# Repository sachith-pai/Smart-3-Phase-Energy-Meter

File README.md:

# Smart-3-Phase-Enrgy-Meter
An ESPHome-based energy meter powered by PZEM-004T V4 and Seed Studio Xiao ESP32-C6/ESP32-C3
 <div align="center">
  
</div>

## Componenets
1. [Seed Studio Xiao C6](https://www.seeedstudio.com/Seeed-Studio-XIAO-ESP32C6-p-5884.html) OR Xiao C3
2. [PZEM-004T V4](https://robu.in/product/pzem-004t-with-coil-ct-with-outcasehot-ac-meter/)
3. [SSD1306 0.96 OLED Display](https://quartzcomponents.com/products/oled-display-0-96-inch-i2c-interface-4-pin-blue-ssd1306)
4. [Hi-Link 5V 5W PSU (HLK 5M05)](https://robu.in/product/hlk-5m05-5v-5w-switch-power-supply-module/?gad_source=1&gad_campaignid=17427802559&gbraid=0AAAAADvLFWdyY2DiddMgGUwxKQrgYGrId&gclid=CjwKCAjwq6DQBhBVEiwA4ZD5XINyfahhBX2IyH8qCKN4hPUuXApgPumztB-3vMhQIovpEZZ0PR9EfBoCjpYQAvD_BwE)
5. [1N5819 Schottky barrier diode](https://robu.in/product/1n5819-1w-diode-pack-of-30/)
6. [4 Pin JST XH Male Connector - 2.54mm pitch](https://quartzcomponents.com/products/4-pin-jst-xh-male-connector-5-24mm-pitch)
7. [4 Pin JST Female to Female Connector - 2.54mm Pitch](https://quartzcomponents.com/products/4-pin-jst-female-to-female-connector-2-54mm-pitch)
8. [2 Pin Screw Terminal Block - 5mm Pitch](https://quartzcomponents.com/products/2-pin-pcb-mount-terminal-block-screw-type)
9. [Transparent Junction Box(180X130X100)](https://amzn.in/d/0d2WMVyG)

## Schematics 
 <div align="center">
  
</div>

> [!NOTE]
>If ESPHome is unable to read from all three PZEM modules simultaneously, it is because multiple devices prevent the signal from dropping close enough to GND. To fix this, it is recommended to place a 1N5819  Schottky diode on the TX line of each PZEM .  Which I have included in the schematics as well as  in the PCB 

## PCB 

<table align="center">
  <tr>
    <td align="center">
      <br>
    </td>
    <td align="center">
      <br>
    </td>

  </tr>
</table>

## Installtion 
1. Download the configuration of your board (c3 or c6), which can be found [HERE](/ESPHOME), and simply go to your ESPHome instance and "import from file" as shown in the picture 
  <div align="center">
  
</div>
2. Set the address to each of the Pzem-004T's using a USB to TTL Serial Adapter as follows

> [!NOTE]
> The address can also be changed in ESPHome, but this is recommended 

|Phase|Address|
|:--:|:--:|
|P1|0x01|
|P2|0x02|
|P3|0x03|

## Reference
1. [ESPHome Pzem-004T Docs](https://esphome.io/components/sensor/pzemac/)
2. [ESPHome SSD1306 OLED Display Docs](https://esphome.io/components/display/ssd1306/)
3. [Multiple Pzem Communication Error forum](https://community.home-assistant.io/t/pzem-004t-v4-0-esphome-not-able-to-read-simultaneously-from-all-3-pzems/957478/2)

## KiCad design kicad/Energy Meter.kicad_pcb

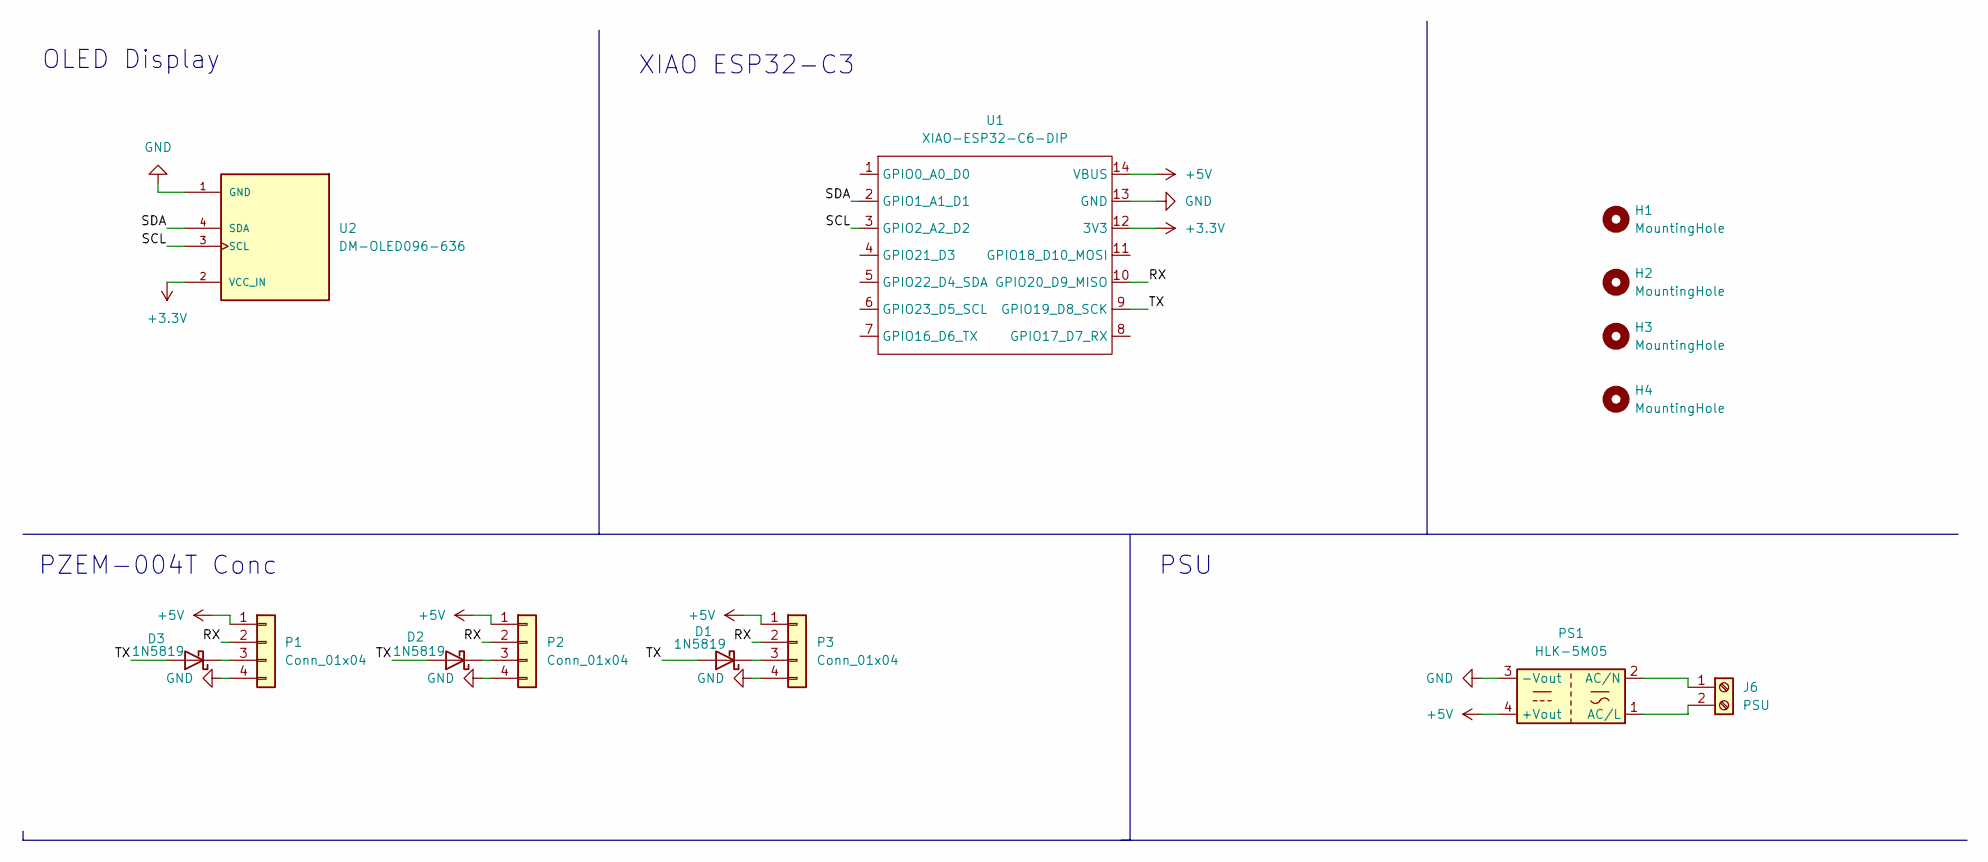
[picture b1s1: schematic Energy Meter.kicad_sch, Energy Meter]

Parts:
D1, D2, D3: 1N5819; D_DO-41_SOD81_P10.16mm_Horizontal
H1, H2, H3, H4: MountingHole; MountingHole_3.2mm_M3_ISO7380_Pad
J6: PSU; TerminalBlock_MaiXu_MX126-5.0-02P_1x02_P5.00mm
P1, P2, P3: Conn_01x04; PinHeader_1x04_P2.54mm_Vertical
PS1: HLK-5M05; Converter_ACDC_Hi-Link_HLK-5Mxx
U1: XIAO-ESP32-C6-DIP
U2: DM-OLED096-636; MODULE_DM-OLED096-636; PARTREV 2018-09-10

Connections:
+3.3V: U1.12 (3V3), U2.2 (VCC_IN)
+5V: P1.1, P2.1, P3.1, PS1.4 (+Vout), U1.14 (VBUS)
/RX: P1.2, P2.2, P3.2, U1.10 (GPIO20_D9_MISO)
/SCL: U1.3 (GPIO2_A2_D2), U2.3 (SCL)
/SDA: U1.2 (GPIO1_A1_D1), U2.4 (SDA)
/TX: D1.2 (A), D2.2 (A), D3.2 (A), U1.9 (GPIO19_D8_SCK)
GND: P1.4, P2.4, P3.4, PS1.3 (-Vout), U1.13 (GND), U2.1 (GND)
unnamed: D1.1 (K), P3.3
unnamed: D2.1 (K), P2.3
unnamed: D3.1 (K), P1.3
unnamed: J6.1, PS1.2 (AC/N)
unnamed: J6.2, PS1.1 (AC/L)

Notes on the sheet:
XIAO ESP32-C3
PSU
OLED Display
PZEM-004T Conc

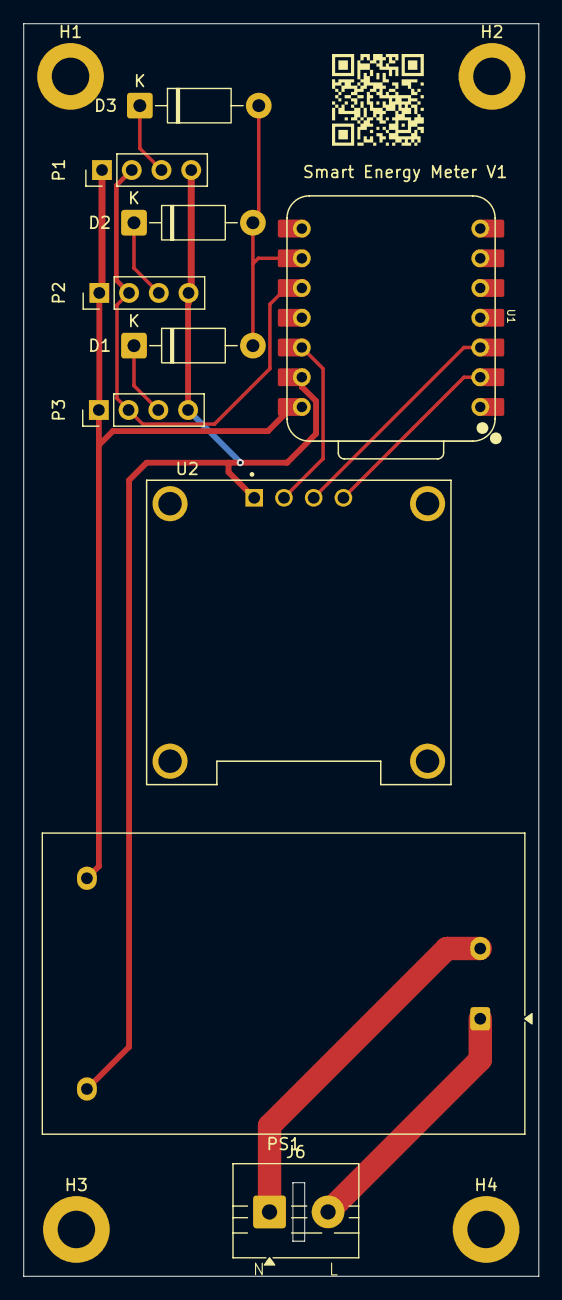
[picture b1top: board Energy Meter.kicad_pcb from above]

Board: 2 copper layers, 44.0 x 107.0 mm, 14 parts (0 on the bottom side), 12 nets.

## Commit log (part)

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2026-05-27 Create Test
